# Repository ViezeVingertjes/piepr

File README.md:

<p align="center">

</p>

<p align="center"><a href="https://piepr.nl/en/">piepr.nl</a> · <a href="README.nl.md">Nederlands</a> · English</p>

**Piepr** is a small open-source reader for Dutch and Belgian smart meters. Plug it
into the meter's P1 port, connect it to WiFi from your phone, and every reading is
available on your own network. No app, no account, no cloud.

- Reads every telegram from the P1 port and checks it (CRC) before passing it on
- Serves the raw telegrams at `piepr.local`, port `8088`, for any software that
  reads P1 data: Home Assistant (DSMR Smart Meter), Domoticz (P1 Smart Meter with LAN
  interface), DSMR-reader, or your own script; up to 5 at the same time
- A status page at `http://piepr.local`: is it reading the meter, the power right
  now, the meter readings
- WiFi setup from your phone, with a list of nearby networks
- Recovers by itself: when it can't join your WiFi, the setup hotspot comes back and
  says why
- About €5 in parts: an ESP32-C3 SuperMini (or a XIAO ESP32-S3), an RJ12 cable, a
  resistor and a diode
- Wired by hand, or on a small [circuit board](hardware/pcb) you can have made

## Using Piepr

1. Plug Piepr into the meter's **P1 port** and into a USB charger.
2. When the light **double-blinks**, join the WiFi network **Piepr-Setup** on your
   phone. The password is **piepr1234**, or your own `setup_pass` if you built the
   firmware yourself. The setup page opens by itself (otherwise browse to
   `http://192.168.4.1` while your phone is on Piepr-Setup).
3. Pick your home network, enter its password and save. Piepr works with
   **2.4 GHz** WiFi only.
4. When the light **stays on**, Piepr is connected. Open `http://piepr.local` in a
   browser to see what your meter says.
5. Point your software at `piepr.local`, port `8088`. In Home Assistant: Settings →
   Devices & services → Add integration → DSMR Smart Meter → Network. DSMR version:
   4 or 5, usually printed on the front of the meter; 5B in Belgium.

To change the WiFi later, hold the **BOOT** button until the light double-blinks
(about 5 seconds).

| Light | Meaning |
|---|---|
| on, with a short flicker per reading | connected and reading the meter |
| blinks evenly | looking for WiFi |
| double blink, then a pause | setup mode: join Piepr-Setup |

| Problem | What to do |
|---|---|
| Piepr-Setup isn't in your WiFi list | wait 5 minutes, or hold BOOT until the light double-blinks |
| Your network isn't listed | it must be 2.4 GHz with a good signal; move the router or an extender closer, or use *Other network…* |
| `piepr.local` doesn't work | find `piepr` in your router's device list and use its IP address |

## Meters

| Meter | P1 version | |
|---|---|---|
| Dutch smart meters | DSMR 4.x, 5.x | supported |
| Belgian digital meters (Fluvius) | e-MUCS P1 | supported; switch the user ports on first at [mijn.fluvius.be/poortbeheer](https://mijn.fluvius.be/poortbeheer) |

Piepr is developed on a Landis+Gyr E350 (DSMR 4.0). Something not working on your
meter? Open a [meter report](https://github.com/ViezeVingertjes/piepr/issues/new?template=meter-report.yml).

## Build your own

1. Hardware: parts list, wiring and checks in the [build guide](hardware/README.md).
2. Firmware: [install it from your browser](https://piepr.nl/en/install/), or build your
   own; see the [firmware guide](firmware/README.md).

| Folder | Contents |
|---|---|
| [`hardware/`](hardware) | Build guide, wiring diagrams and the [circuit board](hardware/pcb) |
| [`firmware/`](firmware) | ESP-IDF firmware, tests and fuzzers |
| [`assets/`](assets) | Logo and images |
| [`tools/`](tools) | A [pretend meter](firmware/docs/simulator.md) for testing, and the image script |

## License

MIT, see [LICENSE](LICENSE). The circuit board in [`hardware/pcb`](hardware/pcb) is under the
CERN Open Hardware Licence v2, Permissive.

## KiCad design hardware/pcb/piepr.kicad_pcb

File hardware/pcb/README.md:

# Piepr P1 board

A small board that replaces the hand-wired cable of the [build guide](../README.md):
the ESP32-C3 SuperMini, an RJ12 socket, the pull-up resistor and two diodes on one
board, connected to the meter with an ordinary RJ12 cable. Revision A.

The pictures show the board with its small parts; the socket and the SuperMini are
left out so that what is under them stays visible.

61.7 × 22.6 mm, two layers, through-hole parts only. Made in KiCad 10; the files open
without anything else installed.

## Parts

| Part | Notes |
|---|---|
| ESP32-C3 SuperMini (not "Plus") with its pin headers soldered on | the pins that are not used go through holes without tracks |
| RJ12 **6P6C** socket for PCBs, horizontal, unshielded: type `95001-6P6C` or `53-6P6C`, or Amphenol 54601-906 | |
| 2.2 kΩ resistor, 1/4 W | 1 to 4.7 kΩ works too |
| 2 × 1N5819 Schottky diode (DO-41) | both with the band towards the capacitor, as printed. The one next to the socket keeps the meter's 5 V out of the board when the cable is the wrong kind; the other keeps USB power out of the meter |
| Optional: 470 µF electrolytic capacitor, 16 V, **8 mm wide, pins 3.5 mm apart** | extra reserve for a DSMR 5 meter that powers the board without USB. To go without, leave its place empty; never bridge it, that would short 5 V to ground |
| RJ12 cable 6P6C, **straight (1:1)** | see below |
| 4 × M3 standoffs and screws | optional; the holes are plated and not connected to anything |

The value of each part is printed on the board under it.

## The cable must be straight

Pin 1 of one plug has to arrive at pin 1 of the other. Many flat telephone cords are
reversed (pin 1 to pin 6). With one of those Piepr does not work: it gets no data, or
stays dark without USB power. The diode next to the socket is there so that nothing
gets damaged. Check a new
cable with a multimeter on continuity before use: hold both plugs the same way, as in
[step 1 of the build guide](../README.md), and the contacts in the same position must
beep.

## Ordering

The board follows [AISLER](https://aisler.net)'s rules for their two-layer boards
(1.6 mm, HASL): upload `piepr.kicad_pcb` as it is. The rules are in the project
(`piepr.kicad_pro`, `piepr.kicad_dru`), so KiCad's own check (Inspect → Design Rules
Checker) tests against them.

## Soldering

The resistor and the diodes first, then the SuperMini, the socket, and last the
capacitor if you use it (long leg in the hole next to the +). The SuperMini goes in with its USB-C
socket over the box marked USB and its `5V` pin in the square pad. Solder everything
on the bottom.

Before plugging anything in, check both diodes with the multimeter's diode test:

| Red probe | Black probe | Reads |
|---|---|---|
| any ground pad (the SuperMini's `G`) | socket pin 6 | 0.15 to 0.35 V; with the probes swapped: no reading |
| socket pin 1 (the square pad) | the SuperMini's `5V` | 0.15 to 0.35 V; with the probes swapped: no reading |

The first row matters most: the board also works with the diode next to the socket
the wrong way round, so this test is the only way to notice.

The SuperMini's pins stick out about 4.5 mm under the board: standoffs must be 5 mm
or longer.

Then [install the firmware](https://piepr.nl/en/install/) and connect it to the meter
as in [step 8 of the build guide](../README.md). With a DSMR 4 meter the board also
needs USB power.

## Licence

Copyright ViezeVingertjes 2026.

This source describes Open Hardware and is licensed under the CERN-OHL-P v2. You may
redistribute and modify it under the terms of the
[CERN-OHL-P v2](https://ohwr.org/cern_ohl_p_v2.txt). It is distributed WITHOUT ANY
EXPRESS OR IMPLIED WARRANTY, INCLUDING OF MERCHANTABILITY, SATISFACTORY QUALITY AND
FITNESS FOR A PARTICULAR PURPOSE. See [LICENSE](LICENSE) for the conditions. The
firmware and the rest of this repository are under the MIT licence.

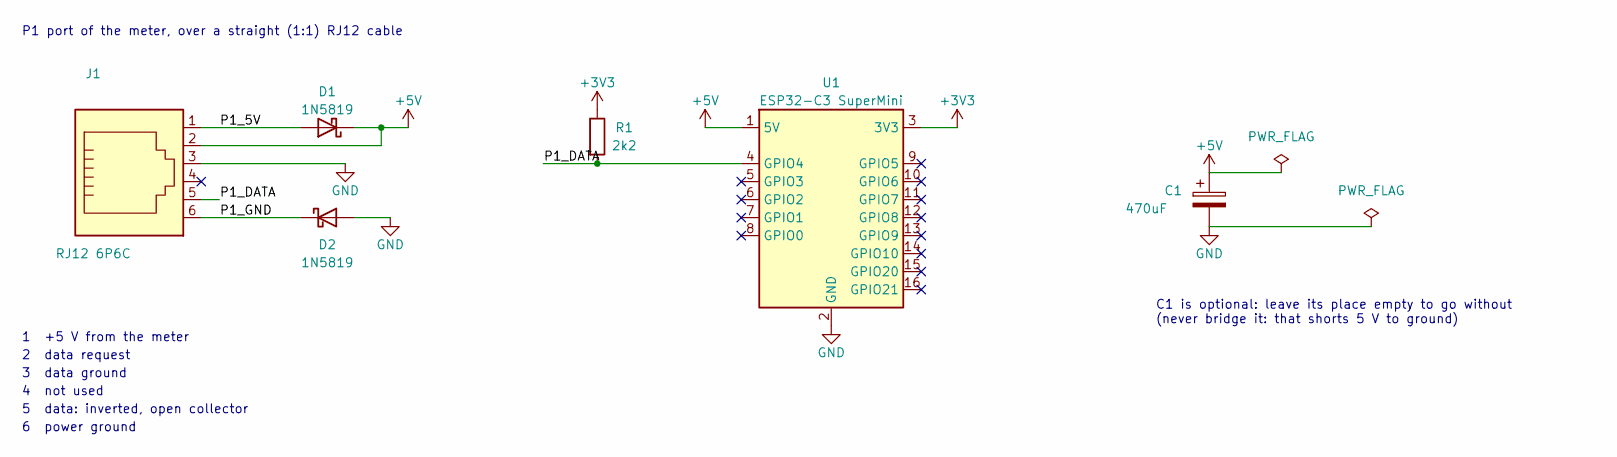
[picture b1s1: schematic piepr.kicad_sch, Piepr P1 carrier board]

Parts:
C1: 470uF; CP_Radial_D8.0mm_P3.50mm
D1, D2: 1N5819; D_DO-41_P10.16mm_Horizontal
J1: RJ12 6P6C; RJ12_6P6C_Horizontal
R1: 2k2; R_Axial_P10.16mm_Horizontal
U1: ESP32-C3 SuperMini; ESP32-C3-SuperMini

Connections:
+3V3: R1.1, U1.3 (3V3)
+5V: C1.1, D1.1 (K), J1.2, U1.1 (5V)
/P1_5V: D1.2 (A), J1.1
/P1_DATA: J1.5, R1.2, U1.4 (GPIO4)
/P1_GND: D2.1 (K), J1.6
GND: C1.2, D2.2 (A), J1.3, U1.2 (GND)

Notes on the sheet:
6 power ground
C1 is optional: leave its place empty to go without (never bridge it: that shorts 5 V to ground)
4 not used
1 +5 V from the meter
5 data: inverted, open collector
P1 port of the meter, over a straight (1:1) RJ12 cable
3 data ground
2 data request

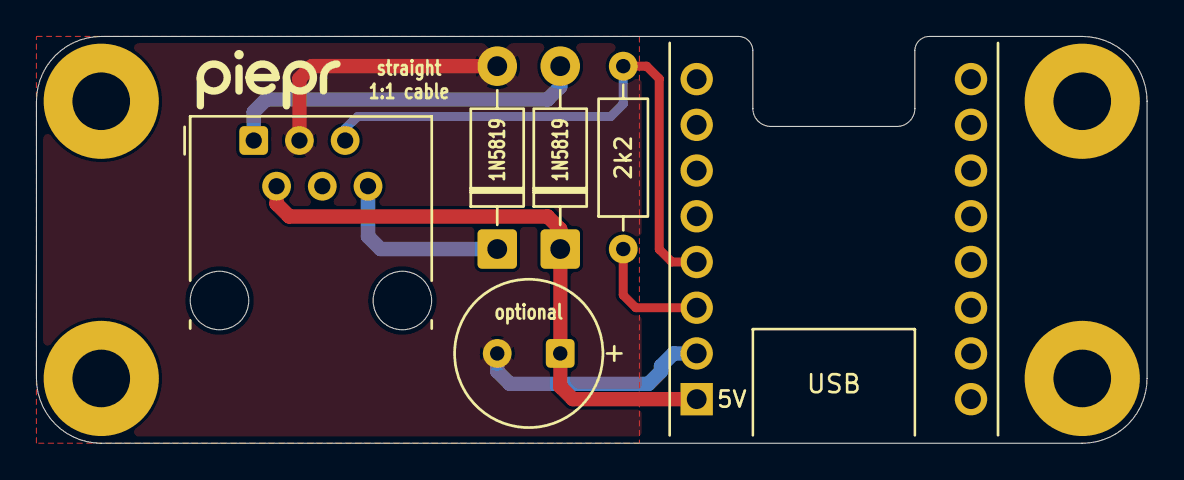
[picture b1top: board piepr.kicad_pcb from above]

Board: 2 copper layers, 61.7 x 22.6 mm, 10 parts (0 on the bottom side), 6 nets.

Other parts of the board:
H1, H2, H3, H4: M3; MountingHole_3.2mm_M3_Pad
